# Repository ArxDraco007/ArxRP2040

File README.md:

# ArxRP2040 - A Custom DevBoard

## Why did I make this project?
Most devboards have limited usability. They don't fit every project. Therefore, it is best that there exists a board that is most customizable, adhering to the purposes that most projects need. This is a basic, very compact devboard that has 24 GPIO pins. This project gives a very good idea of the wiring of devboards and the parts needed to make your own.
This project can be built upon, adding additional parts, extending it, and adding the design.

## Pictures - 

## How to make it?
Follow the schematic and wire the PCB.
Use the Image Converter in KiCad to convert your images to footprints to decorate your PCB.
Download the MicroPython .uf2 file for the RP2040 from micropython.org. Hold the BOOT button (SW1) while plugging in the USB. The board appears as a USB drive. Drag and drop the .uf2 file onto it. Use Thonny IDE or any serial terminal to upload main.py
Start by applying flux to the pads on the footprint where you'll be soldering. Tin one of the pads with a small amount of solder, then carefully place your component onto the footprint. Touch your iron to the tinned pad to reflow it and tack the component in place, then let go with your tweezers once it's sitting right. Move to the opposite pad and solder it properly to the component. Finally, go back to your first pad and add a bit more solder to make sure you've got a solid joint.

## Zine!

## BOM 
| Name | Purpose | Quantity | Total Cost (USD) | Link | Distributor |
|------|---------|----------|-----------------|------|-------------|
| RP2040 | Main MCU (QFN-56) | 1 | $1.00 | [Raspberry Pi]([https://www.digikey.in/en/products/detail/raspberry-pi/SC0914/13624793](https://www.raspberrypi.com/products/rp2040/)) | Raspberry Pi |
| MCP1700x-330xxTT | 3.3V 250mA LDO regulator (SOT-23) | 1 | $0.50 | [DigiKey](https://www.digikey.in/en/products/detail/microchip-technology/MCP1700T-3302E-TT/652676) | DigiKey |
| W25Q16JVZPIQ | 16Mbit QSPI NOR Flash (WSON-8) | 1 | $0.80 | [DigiKey](https://www.digikey.in/en/products/detail/winbond-electronics/W25Q16JVZPIQ/6193781) | DigiKey |
| USB-C Receptacle 14P | HRO TYPE-C-31-M-12 or equiv | 1 | $0.50 | [Hubtronics](https://hubtronics.in/usb-c-female-port?srsltid=AfmBOop8mfonTlbqSHLuMisYp1z4lderBX-p3EpFVBi8DrW3sMfJKgY2) | Hubtronics |
| Conn_01x20 header | 2.54mm 20-pin single row (J3 and J4) | 2 | $1.00 | [Mouser](https://www.mouser.in/ProductDetail/Amphenol-FCI/67996-420HLF?qs=QKvFUfBIyQIvQWWcVN8Heg%3D%3D) | Mouser |
| Conn_01x03 header | 2.54mm 3-pin SWD debug header (J2) | 1 | $0.20 | [Robu](https://robu.in/product/ds1021-03-1x3sf11-b-connfly-1x3-pin-2-54mm-pin-header-single-row-press-fit-type/) | Robu |
| SW_Push tactile switch | BOOT/RUN button (SW1) | 1 | $0.20 | [Digikey](https://www.digikey.in/en/products/detail/alps-alpine/SKRKAEE020/19529176) | Digikey |
| Crystal 12MHz GND24 | SMD 4-pad crystal 3.2x2.5mm (Y1) | 1 | $0.50 | [ETStore](https://www.etstore.in/products/d10953) | ETStore |
| Resistor 5.1K 0402 | CC pull-downs for USB-C (R1, R2) | 2 | $0.10 | [Mouser](https://www.mouser.in/ProductDetail/Vishay-Dale/RCC04025K10FKED?qs=Imq1NPwxi76qRPANg4q4sQ%3D%3D) | Mouser |
| Resistor 27R 0402 | USB D+/D− series resistors (R3, R4) | 2 | $0.10 | [Robu](https://robu.in/product/erj2rkf27r0x-panasonic-smd-chip-resistor-27-ohm-%c2%b1-1-100-mw-0402-1005-metric-thick-film-precision/) | Robu |
| Resistor 1K 0402 | General purpose (R5, R6) | 2 | $0.10 | [Mouser](https://www.mouser.in/ProductDetail/Vishay/CRCW04021K00FHEDP?qs=Vd2sgofiCLVNiwckQwwOyw%3D%3D) | Mouser |
| Resistor 10K 0402 | Pull-up (R7) | 1 | $0.05 | [Robu](https://robu.in/product/rc0402fr-0710kl-yageo-smd-chip-resistor-10-kohm-%C2%B1-1-200-mw-0402-1005-metric-thick-film-pulse-proof-high-power-pack-of-10/) | Robu |
| Capacitor 1uF 0402 | Bulk decoupling (C1, C10) | 2 | $0.20 | [Robu](https://robu.in/product/1uf-capacitor-smdc-0402-pack-of-50/) | Robu |
| Capacitor 0.1uF 0402 | Decoupling (C2–C9, C11, C12, C17) | 11 | $0.55 | [Robu](https://robu.in/product/0402yd104kat2a-kyocera-avx-smd-multilayer-ceramic-capacitor-0-1-%C2%B5f-16-v-0402-1005-metric-%C2%B1-10-x5r-avx-0402-mlcc/) | Robu |
| Capacitor 10uF 0603 | LDO bulk caps (C13, C14) | 2 | $0.30 | [Robu](https://robu.in/product/10uf-10000nf-50v-capacitor-0603-smd-package-pack-of-5/) | Robu |
| Capacitor 33pF 0402 | Crystal load caps (C15, C16) | 2 | $0.20 | [Robu](https://robu.in/product/mc0402n330j500ct-murata-smd-multilayer-ceramic-capacitor-33-pf-50-v-0402-1005-metric-%C2%B1-5-c0g-np0-mc/) | Robu |
| PCB 2-layer ENIG | JLCPCB, 5 boards | 5 | $18.00 | [JLCPCB](https://jlcpcb.com/) | JLCPCB |
| **Total** | | | **$24.30** | | |

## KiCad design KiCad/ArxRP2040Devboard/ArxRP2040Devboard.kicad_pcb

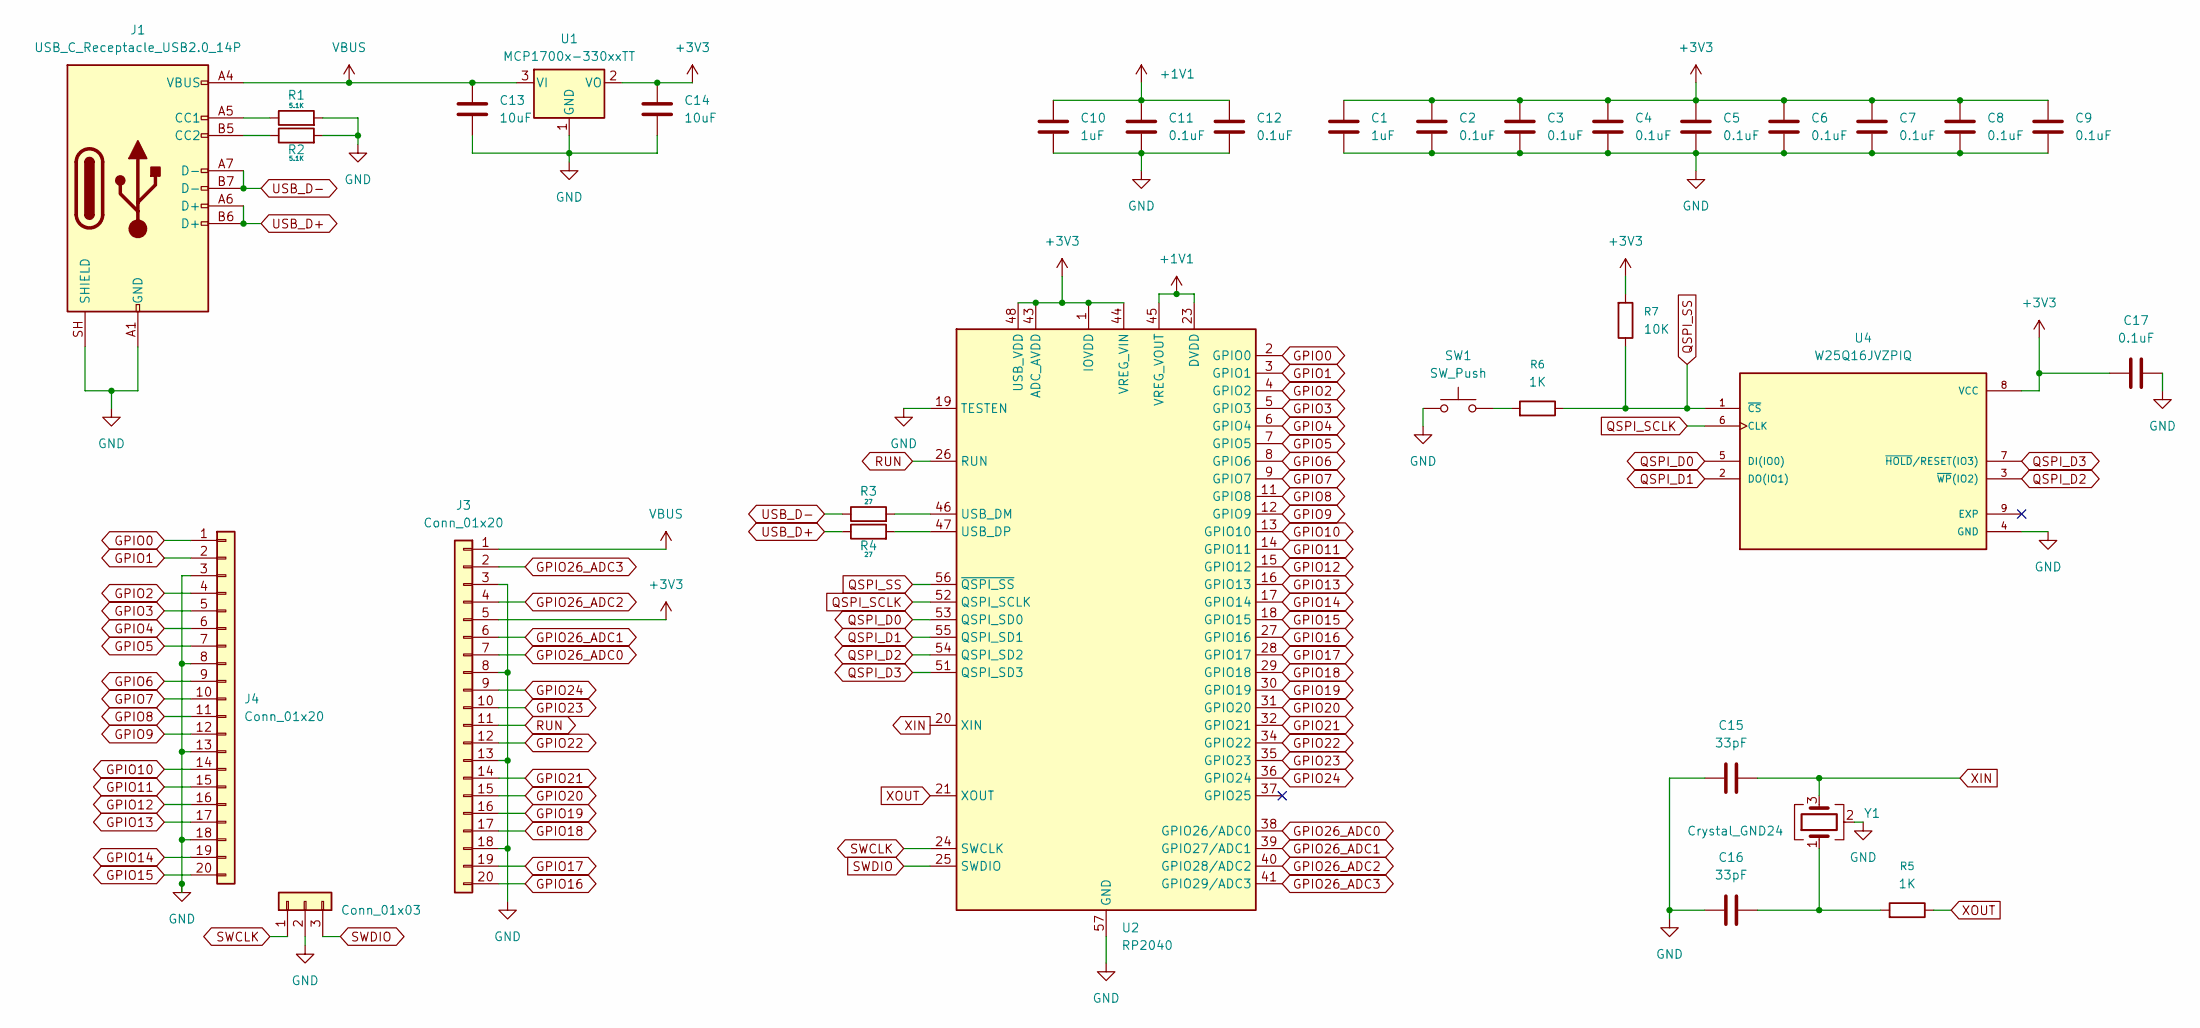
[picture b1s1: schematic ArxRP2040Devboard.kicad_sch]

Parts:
C1, C10: 1uF; C_0402_1005Metric
C2, C3, C4, C5, C6, C7, C8, C9, C11, C12, C17: 0.1uF; C_0402_1005Metric
C13, C14: 10uF; C_0603_1608Metric
C15, C16: 33pF; C_0402_1005Metric
J1: USB_C_Receptacle_USB2.0_14P; USB_C_Receptacle_HRO_TYPE-C-31-M-12
J2: Conn_01x03; PinHeader_1x03_P2.54mm_Vertical
J3, J4: Conn_01x20; PinHeader_1x20_P2.54mm_Vertical
R1, R2: 5.1K; R_0402_1005Metric
R3, R4: 27; R_0402_1005Metric
R5, R6: 1K; R_0402_1005Metric
R7: 10K; R_0402_1005Metric
SW1: SW_Push; SW_Push_SPST_NO_Alps_SKRK
U1: MCP1700x-330xxTT; SOT-23
U2: RP2040; QFN-56-1EP_7x7mm_P0.4mm_EP3.2x3.2mm
U4: W25Q16JVZPIQ; Winbond_USON-8-1EP_3x2mm_P0.5mm_EP0.2x1.6mm
Y1: Crystal_GND24; Crystal_SMD_3225-4Pin_3.2x2.5mm_HandSoldering

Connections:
+1V1: C10.1, C11.1, C12.1, U2.23 (DVDD), U2.45 (VREG_VOUT), U2.50 (DVDD)
+3V3: C1.1, C2.1, C3.1, C4.1, C5.1, C6.1, C7.1, C8.1, C9.1, C14.1, C17.1, J3.5, R7.1, U1.2 (VO), U2.1 (IOVDD), U2.10 (IOVDD), U2.22 (IOVDD), U2.33 (IOVDD), U2.42 (IOVDD), U2.43 (ADC_AVDD), U2.44 (VREG_VIN), U2.48 (USB_VDD), U2.49 (IOVDD), U4.8 (VCC)
GND: C1.2, C2.2, C3.2, C4.2, C5.2, C6.2, C7.2, C8.2, C9.2, C10.2, C11.2, C12.2, C13.2, C14.2, C15.1, C16.1, C17.2, J1.A1 (GND), J1.A12 (GND), J1.B1 (GND), J1.B12 (GND), J1.SH (SHIELD), J2.2, J3.3, J3.8, J3.13, J3.18, J4.3, J4.8, J4.13, J4.18, R1.2, R2.2, SW1.1, U1.1 (GND), U2.19 (TESTEN), U2.57 (GND), U4.4 (GND), Y1.2 (G), Y1.4 (G)
GPIO0: J4.1, U2.2 (GPIO0)
GPIO1: J4.2, U2.3 (GPIO1)
GPIO2: J4.4, U2.4 (GPIO2)
GPIO3: J4.5, U2.5 (GPIO3)
GPIO4: J4.6, U2.6 (GPIO4)
GPIO5: J4.7, U2.7 (GPIO5)
GPIO6: J4.9, U2.8 (GPIO6)
GPIO7: J4.10, U2.9 (GPIO7)
GPIO8: J4.11, U2.11 (GPIO8)
GPIO9: J4.12, U2.12 (GPIO9)
GPIO10: J4.14, U2.13 (GPIO10)
GPIO11: J4.15, U2.14 (GPIO11)
GPIO12: J4.16, U2.15 (GPIO12)
GPIO13: J4.17, U2.16 (GPIO13)
GPIO14: J4.19, U2.17 (GPIO14)
GPIO15: J4.20, U2.18 (GPIO15)
GPIO16: J3.20, U2.27 (GPIO16)
GPIO17: J3.19, U2.28 (GPIO17)
GPIO18: J3.17, U2.29 (GPIO18)
GPIO19: J3.16, U2.30 (GPIO19)
GPIO20: J3.15, U2.31 (GPIO20)
GPIO21: J3.14, U2.32 (GPIO21)
GPIO22: J3.12, U2.34 (GPIO22)
GPIO23: J3.10, U2.35 (GPIO23)
GPIO24: J3.9, U2.36 (GPIO24)
GPIO26_ADC0: J3.7, U2.38 (GPIO26/ADC0)
GPIO26_ADC1: J3.6, U2.39 (GPIO27/ADC1)
GPIO26_ADC2: J3.4, U2.40 (GPIO28/ADC2)
GPIO26_ADC3: J3.2, U2.41 (GPIO29/ADC3)
unnamed: C16.2, R5.1, Y1.1
unnamed: J1.A5 (CC1), R1.1
unnamed: J1.B5 (CC2), R2.1
unnamed: R6.1, SW1.2
unnamed: R3.2, U2.46 (USB_DM)
unnamed: R4.2, U2.47 (USB_DP)
QSPI_D0: U2.53 (QSPI_SD0), U4.5 (DI(IO0))
QSPI_D1: U2.55 (QSPI_SD1), U4.2 (DO(IO1))
QSPI_D2: U2.54 (QSPI_SD2), U4.3 (~WP(IO2))
QSPI_D3: U2.51 (QSPI_SD3), U4.7 (~HOLD/RESET(IO3))
QSPI_SCLK: U2.52 (QSPI_SCLK), U4.6 (CLK)
QSPI_SS: R6.2, R7.2, U2.56 (~QSPI_SS), U4.1 (~CS)
RUN: J3.11, U2.26 (RUN)
SWCLK: J2.1, U2.24 (SWCLK)
SWDIO: J2.3, U2.25 (SWDIO)
USB_D+: J1.A6 (D+), J1.B6 (D+), R4.1
USB_D-: J1.A7 (D-), J1.B7 (D-), R3.1
VBUS: C13.1, J1.A4 (VBUS), J1.A9 (VBUS), J1.B4 (VBUS), J1.B9 (VBUS), J3.1, U1.3 (VI)
XIN: C15.2, U2.20 (XIN), Y1.3
XOUT: R5.2, U2.21 (XOUT)

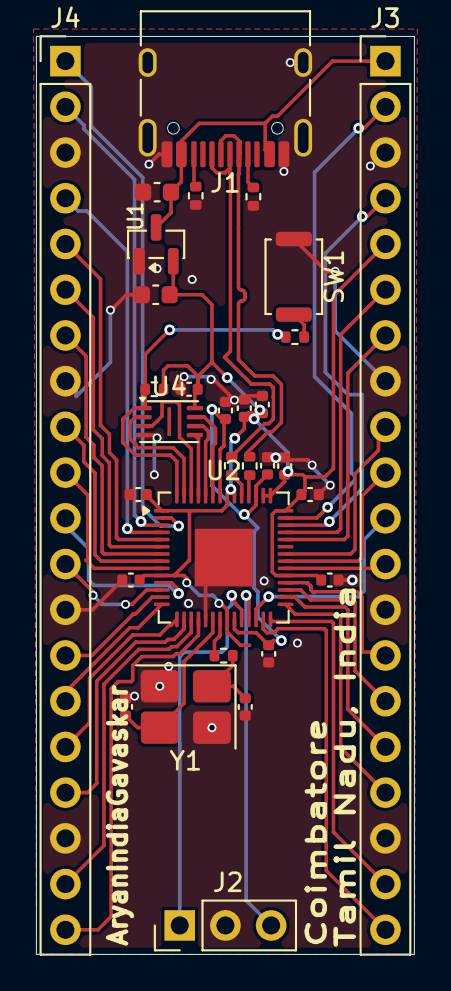
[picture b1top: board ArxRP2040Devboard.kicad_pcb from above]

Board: 2 copper layers, 21.0 x 51.0 mm, 31 parts (0 on the bottom side), 52 nets.

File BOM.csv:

Name,Purpose,Quantity,Total Cost (USD),Link,Distributor
RP2040,Main MCU (QFN-56),1,$1.00,https://www.raspberrypi.com/products/rp2040/,Raspberry Pi
MCP1700x-330xxTT,3.3V 250mA LDO regulator (SOT-23),1,$0.50,https://www.digikey.in/en/products/detail/microchip-technolo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,DigiKey
W25Q16JVZPIQ,16Mbit QSPI NOR Flash (WSON-8),1,$0.80,https://www.digikey.in/en/products/detail/winbond-electronic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,DigiKey
USB-C Receptacle 14P,HRO TYPE-C-31-M-12 or equiv,1,$0.50,https://hubtronics.in/usb-c-female-port,Hubtronics
Conn_01x20 header,2.54mm 20-pin single row (J3 and J4),2,$1.00,https://www.mouser.in/ProductDetail/Amphenol-FCI/67996-420HLF,Mouser
Conn_01x03 header,2.54mm 3-pin SWD debug header (J2),1,$0.20,https://robu.in/product/ds1021-03-1x3sf11-b-connfly-1x3-pin-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,Robu
SW_Push tactile switch,BOOT/RUN button (SW1),1,$0.20,https://www.digikey.in/en/products/detail/alps-alpine/SKRKAE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,Digikey
Crystal 12MHz GND24,SMD 4-pad crystal 3.2x2.5mm (Y1),1,$0.50,https://www.etstore.in/products/d10953,ETStore
Resistor 5.1K 0402,CC pull-downs for USB-C (R1 R2),2,$0.10,https://www.mouser.in/ProductDetail/Vishay-Dale/RCC04025K10FKED,Mouser
Resistor 27R 0402,USB D+/D- series resistors (R3 R4),2,$0.10,https://robu.in/product/erj2rkf27r0x-panasonic-smd-chip-resi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,Robu
Resistor 1K 0402,General purpose (R5 R6),2,$0.10,https://www.mouser.in/ProductDetail/Vishay/CRCW04021K00FHEDP,Mouser
Resistor 10K 0402,Pull-up (R7),1,$0.05,https://robu.in/product/rc0402fr-0710kl-yageo-smd-chip-resis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,Robu
Capacitor 1uF 0402,Bulk decoupling (C1 C10),2,$0.20,https://robu.in/product/1uf-capacitor-smdc-0402-pack-of-50/,Robu
Capacitor 0.1uF 0402,"Decoupling (C2-C9, C11, C12, C17)",11,$0.55,https://robu.in/product/0402yd104kat2a-kyocera-avx-smd-multi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,Robu
Capacitor 10uF 0603,LDO bulk caps (C13 C14),2,$0.30,https://robu.in/product/10uf-10000nf-50v-capacitor-0603-smd-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,Robu
Capacitor 33pF 0402,Crystal load caps (C15 C16),2,$0.20,https://robu.in/product/mc0402n330j500ct-murata-smd-multilay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,Robu
PCB 2-layer ENIG,"JLCPCB, 5 boards",5,$18.00,https://jlcpcb.com/,JLCPCB
Total,,,,$24.30,,

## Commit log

2026-05-05 Kicad
2026-05-05 More connections
2026-05-05 KiCad wiring
2026-05-06 wiring
2026-05-14 Schematic update
2026-06-04 schematics
2026-06-07 PCB Designed!!!!!
2026-06-07 delete
2026-06-07 Gerber
2026-06-07 Add Zine section with image to README
2026-06-07 firmware
2026-06-09 gerber includes the position stuff
2026-06-09 zine changes
2026-06-09 Revise Zine section in README
    Updated Zine section with new title and image.
2026-06-10 zine
